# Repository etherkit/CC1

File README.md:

CC1
===

CC1 CQ QRP Transceiver

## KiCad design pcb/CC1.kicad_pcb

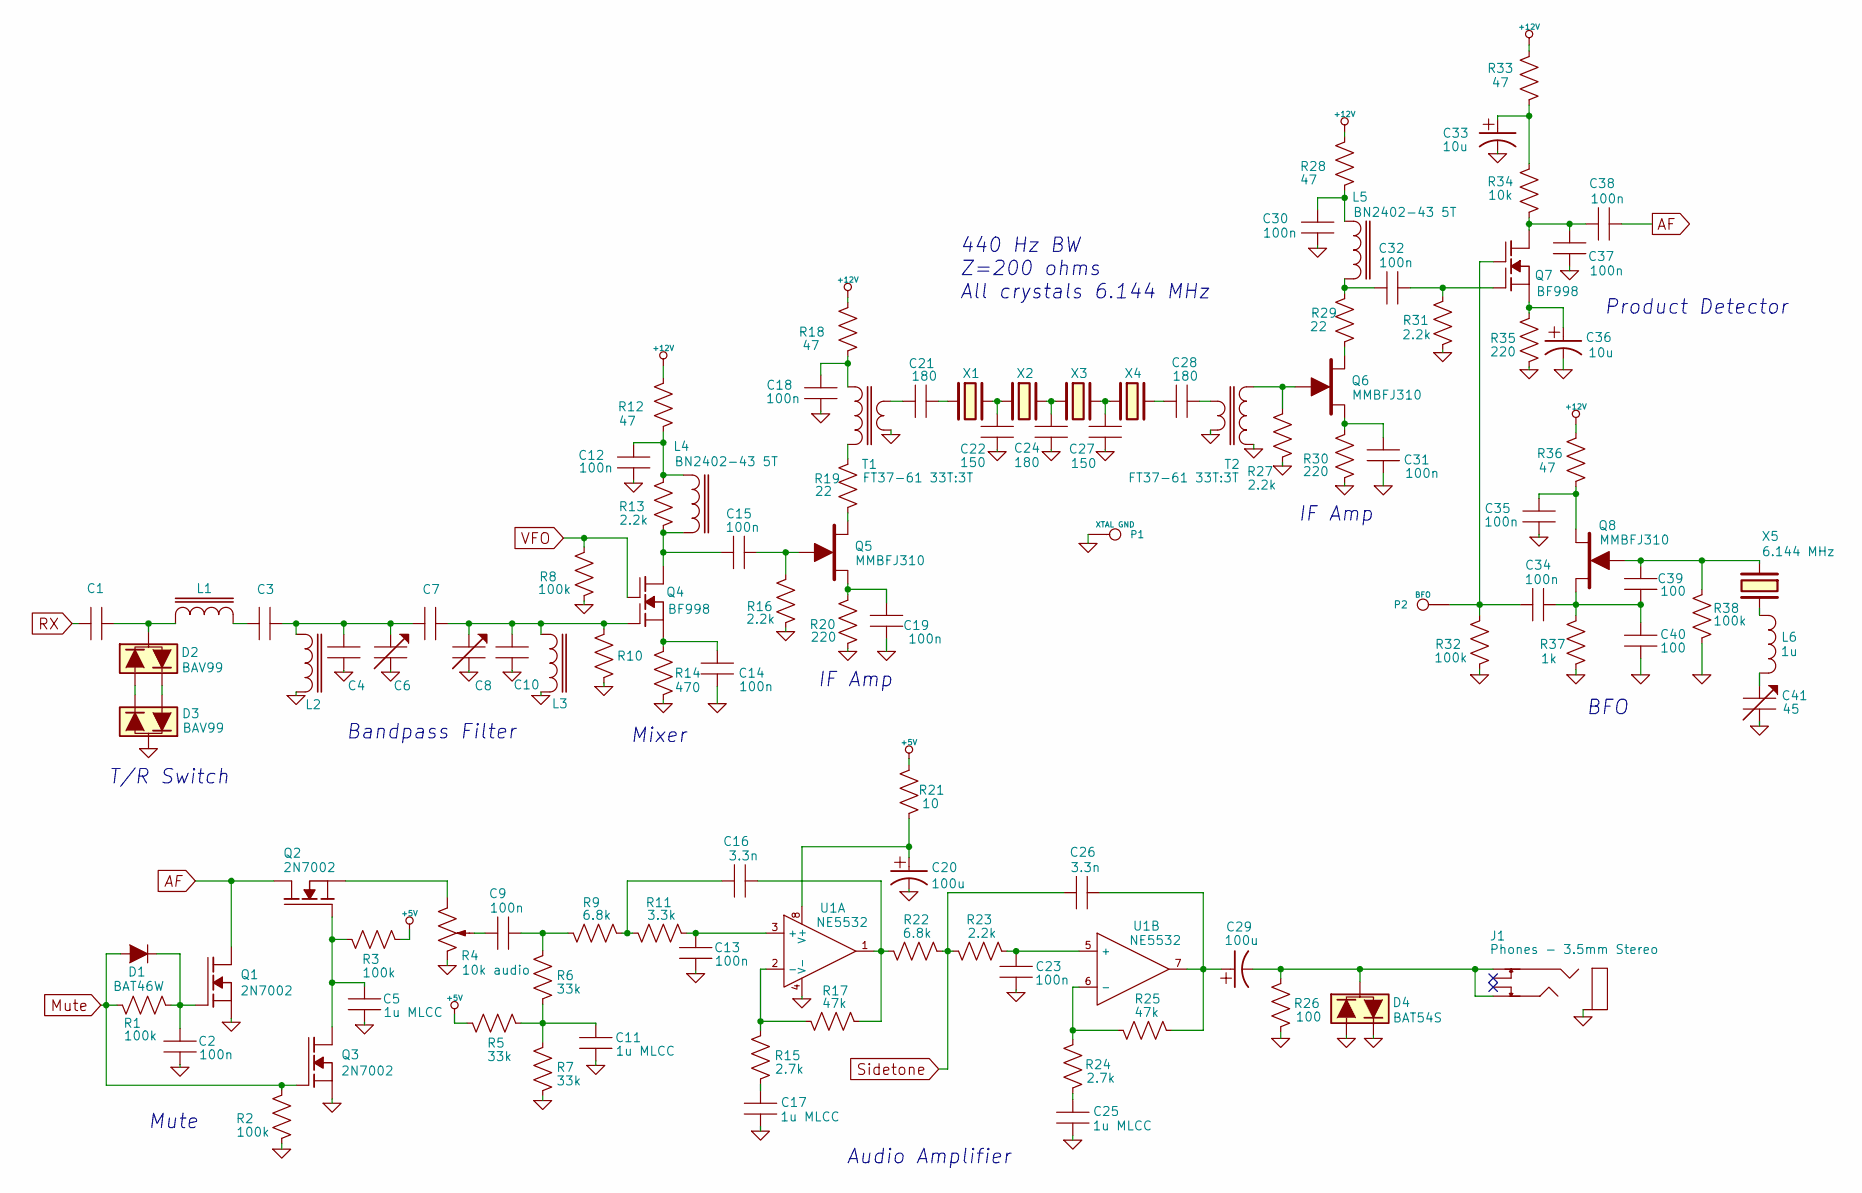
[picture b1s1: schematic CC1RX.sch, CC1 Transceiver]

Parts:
C1, C3, C4, C7, C10: C
C2, C9, C12, C13, C14, C15, C18, C19, C23, C30, C31, C32, C34, C35, C37, C38: 100n
C5, C11, C17, C25: 1u MLCC
C6, C8: CTRIM
C16, C26: 3.3n
C20, C29: 100u
C21, C24, C28: 180
C22, C27: 150
C33, C36: 10u
C39, C40: 100
C41: 45
D1: BAT46W
D2, D3: BAV99
D4: BAT54S
J1: Phones - 3.5mm Stereo
L1, L2, L3: L-IRONCORE
L4, L5: BN2402-43 5T
L6: 1u
P1: XTAL GND
P2: BFO
Q1, Q2, Q3: 2N7002
Q4, Q7: BF998
Q5, Q6, Q8: MMBFJ310
R1, R2, R3, R8, R32, R38: 100k
R4: 10k audio
R5, R6, R7: 33k
R9, R22: 6.8k
R10: R
R11: 3.3k
R12, R18, R28, R33, R36: 47
R13, R16, R23, R27, R31: 2.2k
R14: 470
R15, R24: 2.7k
R17, R25: 47k
R19, R29: 22
R20, R30, R35: 220
R21: 10
R26: 100
R34: 10k
R37: 1k
T1, T2: FT37-61 33T:3T
U1: NE5532
X1, X2, X3, X4, X5: 6.144 MHz

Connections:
+5V: R3.2, R5.1, R21.1; also elsewhere on the board
+12V: R12.1, R18.1, R28.1, R33.1, R36.1; also elsewhere on the board
AF: C38.1, Q1.3 (D), Q2.3 (D)
GND: C2.2, C4.1, C5.2, C6.2, C8.2, C10.1, C11.2, C12.2, C13.2, C14.1, C17.2, C18.2, C19.1, C20.2, C22.2, C23.2, C24.2, C25.2, C27.2, C30.2, C31.1, C33.2, C35.2, C36.2, C37.2, C40.1, C41.2, D3.3, D4.1, D4.2, J1.1, L2.2, L3.2, P1.1, Q1.1 (S), Q3.1 (S), R2.2, R4.3, R7.2, R8.2, R10.2, R14.2, R16.2, R20.2, R26.2, R27.2, R30.2, R31.2, R32.2, R35.2, R37.2, R38.2, T1.4, T2.2, T2.4, U1.4 (V-); also elsewhere on the board
Mute: D1.1 (A), Q3.2 (G), R1.1, R2.1; also elsewhere on the board
unnamed: C18.1, R18.2, T1.1
unnamed: R19.1, T1.2
unnamed: C15.1, Q5.2 (G), R16.1
unnamed: Q5.3 (D), R19.2
unnamed: C21.2, T1.3
unnamed: C21.1, X1.1
unnamed: C28.2, X4.2
unnamed: C28.1, T2.3
unnamed: C12.1, L4.1, R12.2, R13.1
unnamed: C15.2, L4.2, Q4.2 (D), R13.2
unnamed: C24.1, X2.2, X3.1
unnamed: C19.2, Q5.1 (S), R20.1
unnamed: C30.1, L5.1, R28.2
unnamed: Q6.3 (D), R29.2
unnamed: C33.1, R33.2, R34.1
unnamed: C37.1, C38.2, Q7.2 (D), R34.2
unnamed: C27.1, X3.2, X4.1
unnamed: C22.1, X1.2, X2.1
unnamed: C31.2, Q6.1 (S), R30.1
unnamed: Q6.2 (G), R27.1, T2.1
unnamed: C3.1, L1.2
unnamed: R24.1, R25.1, U1.6 (-)
unnamed: C23.1, R23.2, U1.5 (+)
unnamed: C25.1, R24.2
unnamed: C14.2, Q4.1 (S), R14.1
unnamed: C1.2, D2.3, L1.1
unnamed: D2.1, D3.2
unnamed: D2.2, D3.1
unnamed: C7.2, C8.1, C10.2, L3.1, Q4.4 (G1), R10.1
unnamed: C3.2, C4.2, C6.1, C7.1, L2.1
unnamed: C16.2, R9.2, R11.1
unnamed: C20.1, R21.2, U1.8 (V+)
unnamed: C26.1, C29.1, R25.2, U1.7
unnamed: C13.1, R11.2, U1.3 (+)
unnamed: C16.1, R17.2, R22.1, U1.1
unnamed: C17.1, R15.2
unnamed: R15.1, R17.1, U1.2 (-)
unnamed: C29.2, D4.3, J1.2, J1.5, R26.1
unnamed: C9.1, R6.1, R9.1
unnamed: C39.2, Q8.2 (G), R38.1, X5.1
unnamed: C34.1, C39.1, C40.2, Q8.1 (S), R37.1
unnamed: C35.1, Q8.3 (D), R36.2
unnamed: C32.1, Q7.4 (G1), R31.1
unnamed: C36.1, Q7.1 (S), R35.1
unnamed: C32.2, L5.2, R29.1
unnamed: C34.2, P2.1, Q7.3 (G2), R32.1
unnamed: C41.1, L6.2
unnamed: L6.1, X5.2
unnamed: C5.1, Q2.2 (G), Q3.3 (D), R3.1
unnamed: Q2.1 (S), R4.1
unnamed: C9.2, R4.2
unnamed: C11.1, R5.2, R6.2, R7.1
unnamed: C2.1, D1.2 (K), Q1.2 (G), R1.2
RX: C1.1; also elsewhere on the board
Sidetone: C26.2, R22.2, R23.1; also elsewhere on the board
VFO: Q4.3 (G2), R8.1; also elsewhere on the board

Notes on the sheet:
BFO
440 Hz BW Z=200 ohms All crystals 6.144 MHz
Mute
Product Detector
IF Amp
Mixer
Bandpass Filter
T/R Switch
Audio Amplifier

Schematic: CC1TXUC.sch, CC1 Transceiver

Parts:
C42, C43, C44, C45, C46, C47, C48, C49, C50, C52, C53, C54, C55, C57, C58, C59, C60, C62, C63: 100n
C51: 100u
C56, C64, C69: 1u MLCC
C61, C65, C71, C72, C74, C76: 10n
C66, C75: 4.7u MLCC
C67: 22
C68, C73: 39
C70: 68
D5, D7: BZV55-B15
D6: Lumex SSF-LXH240GID
J2: 3.5 mm stereo
J3: I2C
J4: AVR-ISP-6
J5: UART
J6: GPS
J7: ADC
J8: +12VDC
J9: BNC
L7, L8: FT37-43 10T
L9, L10, L11: L-IRONCORE
L12, L13: T37-2 21T
P3: TX Drive
P5: +3.3V
P6: +12V
P7: GND
P8: +5V
P9: VFO
Q9: FDS86106
Q10: IRLML9301
R39, R40, R43, R44, R45: 33k
R41: 5k
R42, R46: 10k
R47, R49, R58, R60: 4.7k
R48: 22k
R50: 100
R51: 47k
R52, R53: 1k
R54: 6.8k
R55, R56: 200
R57: 100k
R59: 220
R61: 2.2k
R62: 51
S1: FREQ
S2: CMD
S3: BI EN12-VS11AF18
U2: 74AC08
U3: ATMEGA328P; MODULE
U4: VCC1-B3D-50M0000000
U5: AD9834
U6: LP2985-3.3
U7: LP2985-5
U8: OPA820IDBVT

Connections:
+3.3V: C66.2, P5.1, U4.1 (OE), U4.4 (VDD), U6.5 (VOUT)
+5V: C45.2, C50.2, C58.2, C61.1, C75.2, J3.1, J4.2, J5.1, J6.2, P8.1, R39.1, R46.1, R47.1, R49.1, R58.2, U2.14 (VCC), U3.4, U3.6, U3.18, U3.20, U5.4 (AVDD), U5.5 (DVDD), U7.5 (VOUT), U8.5 (V+); also elsewhere on the board
+12V: C64.2, C69.2, D7.2 (K), L7.1, P6.1, Q10.1 (S), R51.1, U6.1 (VIN), U6.3 (ON), U7.1 (VIN), U7.3 (ON); also elsewhere on the board
ADC6: J7.1, U3.19
ADC7: J7.2 (PM), U3.22
ENC_A: S3.1 (A), U3.12
ENC_B: S3.3 (B), U3.11
ENC_SW: S3.4 (SW), U3.26
FSYNC: U3.13, U5.15 (FSYNC)
GND: C44.1, C45.1, C46.1, C47.1, C48.1, C49.1, C50.1, C51.2, C52.1, C54.1, C55.1, C56.1, C57.1, C58.1, C59.2, C60.1, C62.1, C63.2, C64.1, C65.1, C66.1, C67.2, C68.1, C69.1, C70.1, C71.1, C72.1, C73.1, C75.1, D5.1 (A), D6.3 (K), D6.4 (K), J2.1, J3.4, J4.6, J5.4, J6.1, J7.3, J8.2 (PM), J8.3, J9.2 (Ext), P7.1, Q9.1 (S), Q9.2 (S), Q9.3 (S), R40.2, R41.3, R48.2, R50.2, R54.1, R55.2, R56.1, R57.2, R60.2, R62.2, S1.1, S2.1, S3.2, S3.5 (SW), U2.7 (GND), U3.3, U3.5, U3.21, U4.2 (GND), U5.7 (DGND), U5.9 (FSELECT), U5.10 (PSELECT), U5.11 (RESET), U5.12 (SLEEP), U5.18 (AGND), U6.2 (GND), U7.2 (GND), U8.2 (V-); also elsewhere on the board
Key: R42.2, U3.8
Mute: U3.7; also elsewhere on the board
unnamed: C61.2, U5.3 (COMP)
unnamed: C63.1, R54.2, U5.1 (FSADJUST)
unnamed: C56.2, C60.2, U5.6 (CAP2.5V)
unnamed: C59.1, U5.2 (REFOUT)
unnamed: C67.1, R56.2, U5.20 (IOUTB)
unnamed: C68.2, L12.1, R55.1, U5.19 (IOUT)
unnamed: C70.2, L12.2, L13.1
unnamed: C73.2, C74.1, L13.2
unnamed: U4.3 (OUT), U5.8 (MCLK)
unnamed: C71.2, U7.4 (BP)
unnamed: C65.2, U6.4 (BP)
unnamed: D7.1 (A), Q10.2 (G), R57.1
unnamed: C44.2, R42.1, U2.2
unnamed: C72.2, R58.1, R60.1, U8.3 (+)
unnamed: R59.1, R61.2, U8.4 (-)
unnamed: C74.2, R59.2
unnamed: J8.1, Q10.3 (D)
unnamed: C76.1, R61.1, R62.1, U8.1
unnamed: C51.1, C52.2, L7.2, L8.1
unnamed: C53.1, D5.2 (K), L8.2, Q9.5 (D), Q9.6 (D), Q9.7 (D), Q9.8 (D)
unnamed: C62.2, J9.1 (In), L11.2
unnamed: C57.2, L10.2, L11.1
unnamed: C55.2, L9.2, L10.1
unnamed: J2.5, U3.1
unnamed: J2.2, U3.2
unnamed: C43.2, R39.2, R40.1, U2.1
unnamed: U2.3, U2.4, U2.5, U2.9, U2.10, U2.12, U2.13
unnamed: P3.1, Q9.4 (G), R50.1, U2.6, U2.8, U2.11
unnamed: D6.2 (A), R52.1
unnamed: R52.2, U3.24
unnamed: D6.1 (A), R53.1
unnamed: R53.2, U3.23
unnamed: R48.1, R51.2, U3.25
unnamed: S2.2, U3.9
unnamed: S1.2, U3.32
unnamed: R45.1, U3.10
unnamed: C48.2, R44.1, R45.2
unnamed: C47.2, R43.1, R44.2
unnamed: C46.2, R41.1, R43.2
unnamed: J4.1, U3.16
unnamed: C42.2, R41.2
RESET: C49.2, J4.5, R46.2, U3.29
RX: C53.2, C54.2, L9.1; also elsewhere on the board
SCA: J3.2, R49.2, U3.27
SCL: J3.3, R47.2, U3.28
SCLK: J4.3, U3.17, U5.14 (SCLK)
SDATA: J4.4, U3.15, U5.13 (SDATA)
Sidetone: C42.1; also elsewhere on the board
UART_RX: J5.2, J6.4, U3.30
UART_TX: J5.3, J6.3, U3.31
VFO: C43.1, C76.2, P9.1; also elsewhere on the board

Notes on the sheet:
Transmit Buffer
Transmit Power Amp
Transmit Low-Pass Filter
Key/Paddles
Microcontroller
DDS VFO
Power Conditioning

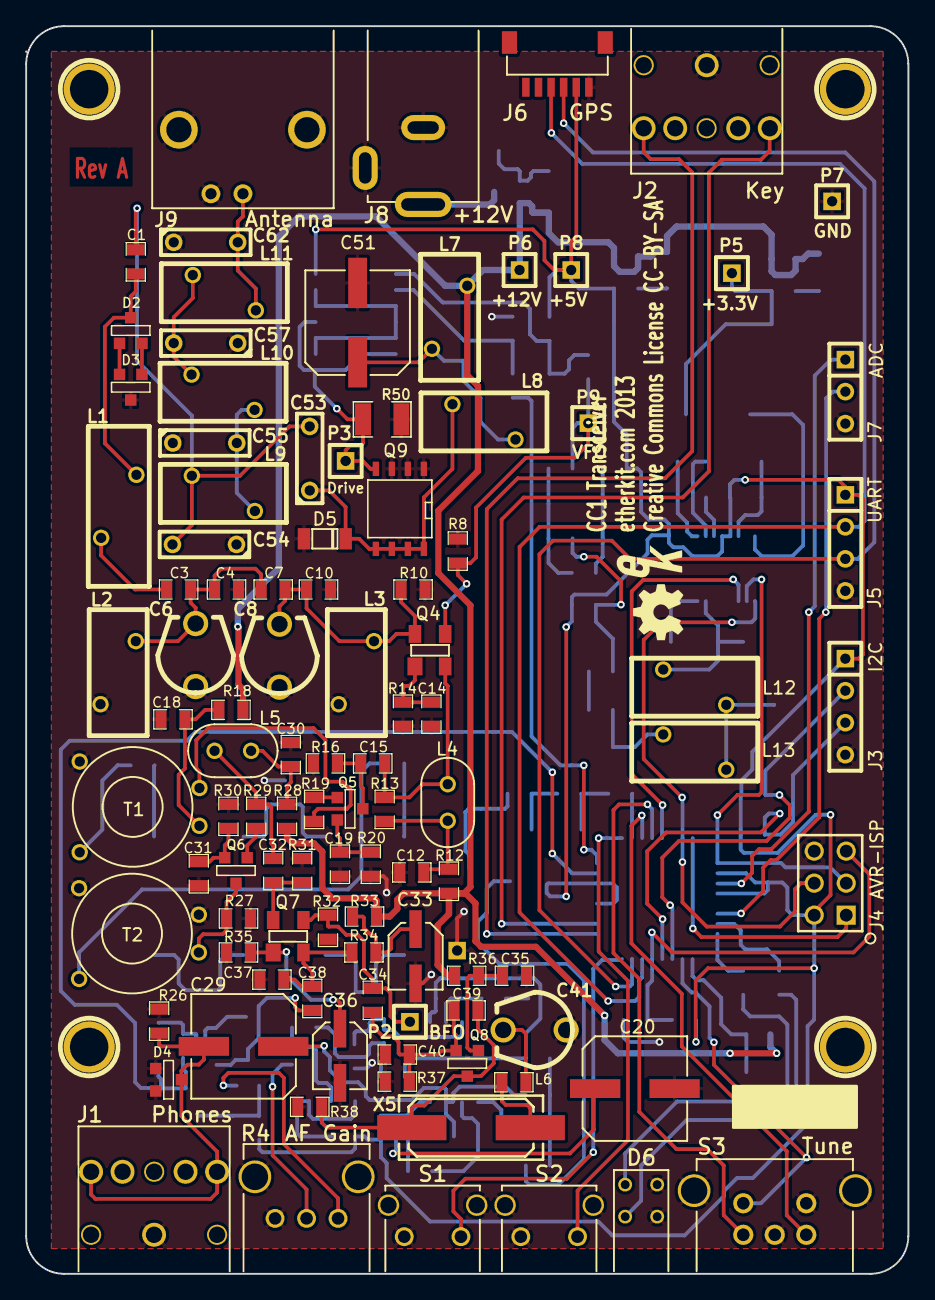
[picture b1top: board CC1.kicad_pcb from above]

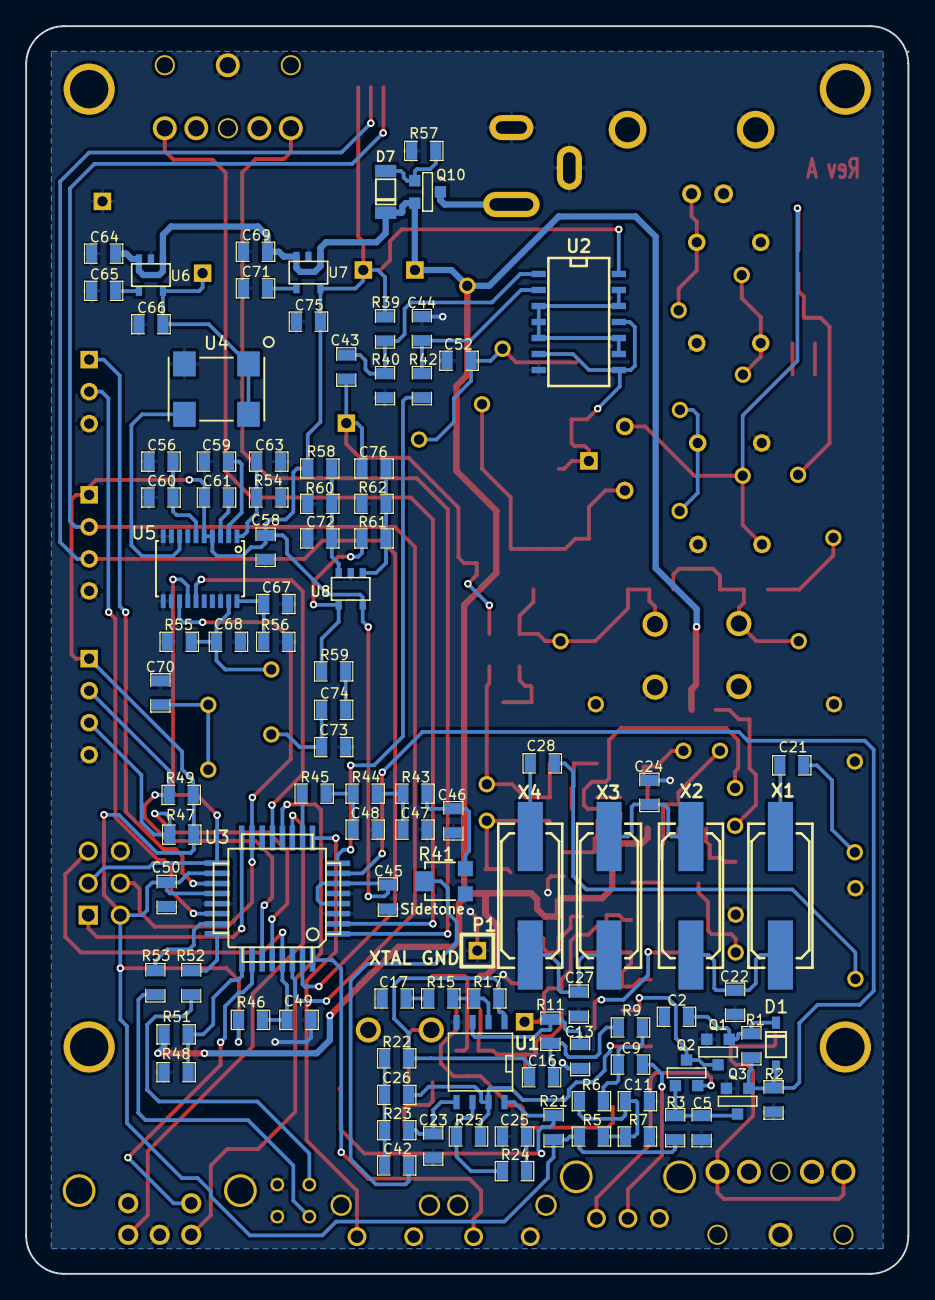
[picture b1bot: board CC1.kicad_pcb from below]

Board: 2 copper layers, 70.0 x 99.0 mm, 208 parts (101 on the bottom side), 117 nets.

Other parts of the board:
1PIN, 1PIN#2, 1PIN#3, 1PIN#4: P***; MOUNTINGHOLE
Ref**: Val**; EtherkitLogoSmall

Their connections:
GND: 1PIN.1, 1PIN#2.1, 1PIN#3.1, 1PIN#4.1; also elsewhere on the board

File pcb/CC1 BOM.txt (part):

eeschema (2013-feb-21)-testing  >> Creation date: Sun 24 Feb 2013 09:59:55 AM PST
#Cmp ( order = Reference )
| C1         C           
| C2         100n        
| C3         C           
| C4         C           
| C5         1u MLCC     
| C6         CTRIM       
| C7         C           
| C8         CTRIM       
| C9         100n        
| C10        C           
| C11        4.7u MLCC   
| C12        100n        
| C13        100n        
| C14        100n        
| C15        100n        
| C16        3.3n        
| C17        1u MLCC     
| C18        100n        
| C19        100n        
| C20        100u        
| C21        120         
| C22        100         
| C23        100n        
| C24        120         
| C25        1u MLCC     
| C26        3.3n        
| C27        100         
| C28        120         
| C29        100u        
| C30        100n        
| C31        100n        
| C32        100n        
| C33        10u         
| C34        33          
| C35        100n        
| C36        10u         
| C37        10n         
| C38        100n        
| C39        33          
| C40        33          
| C41        45          
| C42        10n         
| C43        100n        
| C44        100n        
| C45        100n        
| C46        100n        
| C47        100n        
| C48        100n        
| C49        100n        
| C50        100n        
| C51        100u        
| C52        100n        
| C53        100n        
| C54        100n        
| C55        100n        
| C56        1u MLCC     
| C57        100n        
| C58        100n        
| C59        100n        
| C60        100n        
| C61        10n         
| C62        100n        
| C63        100n        
| C64        1u MLCC     
| C65        10n         
| C66        4.7u MLCC   
| C67        22          
| C68        39          
| C69        1u MLCC     
| C70        68          
| C71        10n         
| C72        10n         
| C73        39          
| C74        10n         
| C75        4.7u MLCC   
| C76        10n         
| D1         BAT46W      
| D2         BAV99       
| D3         BAV99       
| D4         BAT54S      
| D5         BZV55-B33   
| D6         Lumex SSF-LXH240GID
| D7         BZV55-B15   
| J1         Phones - 3.5mm Stereo
| J2         3.5 mm stereo
| J3         I2C         
| J4         AVR-ISP-6   
| J5         UART        
| J6         GPS         
| J7         ADC         
| J8         +12VDC      
| J9         BNC         
| L1         L-IRONCORE  
| L2         L-IRONCORE  
| L3         L-IRONCORE  
| L4         BN2402-43 5T
| L5         BN2402-43 5T
| L6         22u         
| L7         FT37-43 10T 
| L8         FT37-43 10T 
| L9         L-IRONCORE  
| L10        L-IRONCORE  
| L11        L-IRONCORE  
| L12        T37-2 21T   
| L13        T37-2 21T   
| P1         XTAL GND    
| P2         BFO         
| P3         TX Drive    
| P5         +3.3V       
| P6         +12V        
| P7         GND         
| P8         +5V         
| P9         VFO         
| Q1         2N7002      
| Q2         2N7002      
| Q3         2N7002      
| Q4         BF998       
| Q5         MMBFJ310    
| Q6         MMBFJ310    
| Q7         BF998       
| Q8         MMBFJ310    
| Q9         FDS86106    
| Q10        IRLML9301   
| R1         100k        
| R2         100k        
| R3         100k        
| R4         10k audio   
| R5         100k        
| R6         1M          
| R7         100k        
| R8         100k        
| R9         6.8k        
| R10        R           
| R11        3.3k        
| R12        47          
| R13        2.2k        
| R14        470         
| R15        4.7k        
| R16        2.2k        
| R17        47k         
| R18        47          
| R19        10          
| R20        1k          
| R21        10          
| R22        6.8k        
| R23        2.2k        
| R24        4.7k        
| R25        47k         
| R26        100         
| R27        220         
| R28        47          
| R29        10          
| R30        1k          
| R31        2.2k        
| R32        2.2k        
| R33        47          
| R34        2.2k        
| R35        470         
| R36        47          
| R37        1k          
| R38        100k        
| R39        33k         
| R40        33k         
| R41        5k          
| R42        10k         
| R43        10k         
| R44        10k         
| R45        10k         
| R46        10k         
| R47        4.7k        
| R48        22k         
| R49        4.7k        
| R50        100         
| R51        47k         
| R52        1k          
| R53        1k          
| R54        6.8k        
| R55        200         
| R56        200         
| R57        100k        
| R58        4.7k        
| R59        220         
| R60        4.7k        
| R61        3.3k        
| R62        47          
| S1         FREQ        
| S2         CMD         
| S3         BI EN12-VS11AF18
| T1         FT37-43 20T:5T
| U1         NE5532      
| U2         74AC08      
| U3         ATMEGA328P  
| U4         VCC1-B3D-50M0000000
| U5         AD9834      
| U6         LP2985-3.3  
| U7         LP2985-5    
| U8         OPA820IDBVT 
| X1         6.144 MHz   
| X2         6.144 MHz   
| X3         6.144 MHz   
| X4         6.144 MHz   
| X5         4.9152 MHz  
#End Cmp

#Cmp ( order = Value )
| 3.3n         C16       
| 3.3n         C26       
| 10n          C37       
| 10n          C42       
| 10n          C61       
| 10n          C65       
| 10n          C71       
| 10n          C72       
| 10n          C74       
| 10n          C76       
| 100n         C2        
| 100n         C9        
| 100n         C12       
| 100n         C13       
| 100n         C14       
| 100n         C15       
| 100n         C18       
| 100n         C19       
| 100n         C23       
| 100n         C30       
| 100n         C31       
| 100n         C32       
| 100n         C35       
| 100n         C38       
| 100n         C43       
| 100n         C44       
| 100n         C45       
| 100n         C46       
| 100n         C47       
| 100n         C48       
| 100n         C49       
| 100n         C50       
| 100n         C52       
| 100n         C53       
| 100n         C54       
| 100n         C55       
| 100n         C57       
| 100n         C58       
| 100n         C59       
| 100n         C60       
| 100n         C62       
| 100n         C63       
| 1u MLCC      C5        
| 1u MLCC      C17       
| 1u MLCC      C25       
| 1u MLCC      C56       
| 1u MLCC      C64       
| 1u MLCC      C69       
| 4.7u MLCC    C11       
| 4.7u MLCC    C66       
| 4.7u MLCC    C75       
| 10u          C33       
| 10u          C36       
| 100u         C20       
| 100u         C29       
| 100u         C51       
| 22           C67       
| 33           C34       
| 33           C39       
| 33           C40       
| 39           C68       
| 39           C73       
| 45           C41       
| 68           C70       
| 100          C22       
| 100          C27       
| 120          C21       
| 120          C24       
| 120          C28       
| C            C1        
| C            C3        
| C            C4        
| CTRIM        C6        
| C            C7        
| CTRIM        C8        
| C            C10       
| BAT46W       D1        
| BAV99        D2        
| BAV99        D3        
| BAT54S       D4        
| BZV55-B33    D5        
| Lumex SSF-LXH240GID D6        
| BZV55-B15    D7        
| 3.5 mm stereo J2        
| Phones - 3.5mm Stereo J1        
| I2C          J3        
| UART         J5        
| GPS          J6        
| ADC          J7        
| +12VDC       J8        
| BNC          J9        
| AVR-ISP-6    J4        
| 22u          L6        
| L-IRONCORE   L1        
| L-IRONCORE   L2        
| L-IRONCORE   L3        
| BN2402-43 5T L4        
| BN2402-43 5T L5        
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
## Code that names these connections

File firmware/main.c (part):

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#include "sinewave.h"

// Input and output pin definitions
#define	SIDETONE				PD6			// Sidetone output
#define SIDETONE_PORT			PORTD		// Sidetone output port
#define SIDETONE_DDR			DDRD		// Sidetone output DDR

#define PADDLE_DIT				PD3			// Dit paddle
#define PADDLE_DIT_PORT			PORTD		// Dit paddle port
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#define MSG_BUTTON_PIN			PIND
#define MSG_BUTTON_PC			PCINT21

#define ENC_A					PB0			// Rotary encoder A output
#define ENC_A_PORT				PORTB
#define ENC_A_DDR				DDRB
#define ENC_A_PIN				PINB
#define ENC_A_PC				PCINT0

#define ENC_B					PD7			// Rotary encoder B output
#define ENC_B_PORT				PORTD
#define ENC_B_DDR				DDRD
#define ENC_B_PIN				PIND
#define ENC_B_PC				PCINT23

#define ENC_BUTTON				PC3			// Rotary encoder button
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#define ENC_BUTTON_PIN			PINC
#define ENC_BUTTON_PC			PCINT11

#define MUTE					PB6			// Mute output
#define MUTE_PORT				PORTB
#define MUTE_DDR				DDRB

#define TX						PB7			// Transmit output
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#define MAX_WPM					40			// Maximum WPM setting
#define TX_ON_DELAY				2			// TX sequence delay time (in 1 ms increments)
#define TX_OFF_DELAY			3
#define MUTE_OFF_DELAY			20			// Mute off delay time (in 1 ms increments)
#define ANNOUNCE_BUFFER_SIZE	41			// Buffer size for announce string
#define MENU_EXPIRATION			4000		// Menu expiration time (in 1 ms increments)
#define REC_EXPIRATION			1000		// Keyer memory character record expiration
#define REC_SPACE_EXPIRATION	2000		// Keyer memory space character expiration
#define MSG_BUFFER_SIZE			41			// Keyer message size in characters
#define SLEEP_DELAY				300			// Time (in ms) to delay before going to sleep because of inactivity
#define ST_REFCLK				429497		// Sidetone DDS ref clock - 2^32 / 10 kHz sample rate
#define ST_DEFAULT				600			// Default sidetone frequency
#define ST_HIGH					900			// High sidetone frequency
#define ST_LOW					400			// Low sidetone frequency

// DDS tuning steps (50 MHz master clock)
#define DDS_20HZ				0x1B
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// Band constants
// 40 Meters
#ifdef BAND_40M
#define DDS_INIT				0x3D2806B	// AD9834 w/ 50 MHz Fc, 11.945 MHz VFO - 600 Hz shift
#define DDS_TX_INIT				0x23FE5C9
#define FREQ_INIT				7030000
#define LOWER_FREQ_LIMIT		7000000
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
// 20 Meters
#ifdef BAND_20M
#define DDS_INIT				0x6126634 	// AD9834 w/ 50 MHz Fc, 18.9752 MHz VFO + 600 Hz shift
#define DDS_TX_INIT				0x47FCB92
#define FREQ_INIT				14060000
#define LOWER_FREQ_LIMIT		14000000
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

	// Debounce Encoder A
	if(bit_is_clear(ENC_A_PIN, ENC_A))
	{
		if(enca_on_count < DEBOUNCE_PRESS_TIME)
			enca_on_count++;
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

	// Debounce Encoder B
	if(bit_is_clear(ENC_B_PIN, ENC_B))
	{
		if(encb_on_count < DEBOUNCE_PRESS_TIME)
			encb_on_count++;
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
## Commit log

2013-01-31 First commit, conversion to CC1
2013-01-31 README
2013-01-31 Update schematics for beta
2013-02-03 Added basic keyer record function
2013-02-03 Completed keyer record for both message memories, added space and erase char
2013-02-24 Beta test 1
2013-02-25 Minor correction for Beta 1
2013-02-25 A few more changes on Beta 1
2013-03-20 Minor typo correction on BOM
2013-04-07 Firmware fix for RX osc hash
2013-04-14 Change to T1 and L5 in schematics/BOM
2013-04-14 Put band define in build config

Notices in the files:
firmware/main.c:
Copyright (c) 2013, Jason Milldrum
All rights reserved.
pcb/CC1.kicad_pcb:
Creative Commons License CC-BY-SA
pcb/CC1RX.sch:
Creative Commons Licence CC-BY-SA
